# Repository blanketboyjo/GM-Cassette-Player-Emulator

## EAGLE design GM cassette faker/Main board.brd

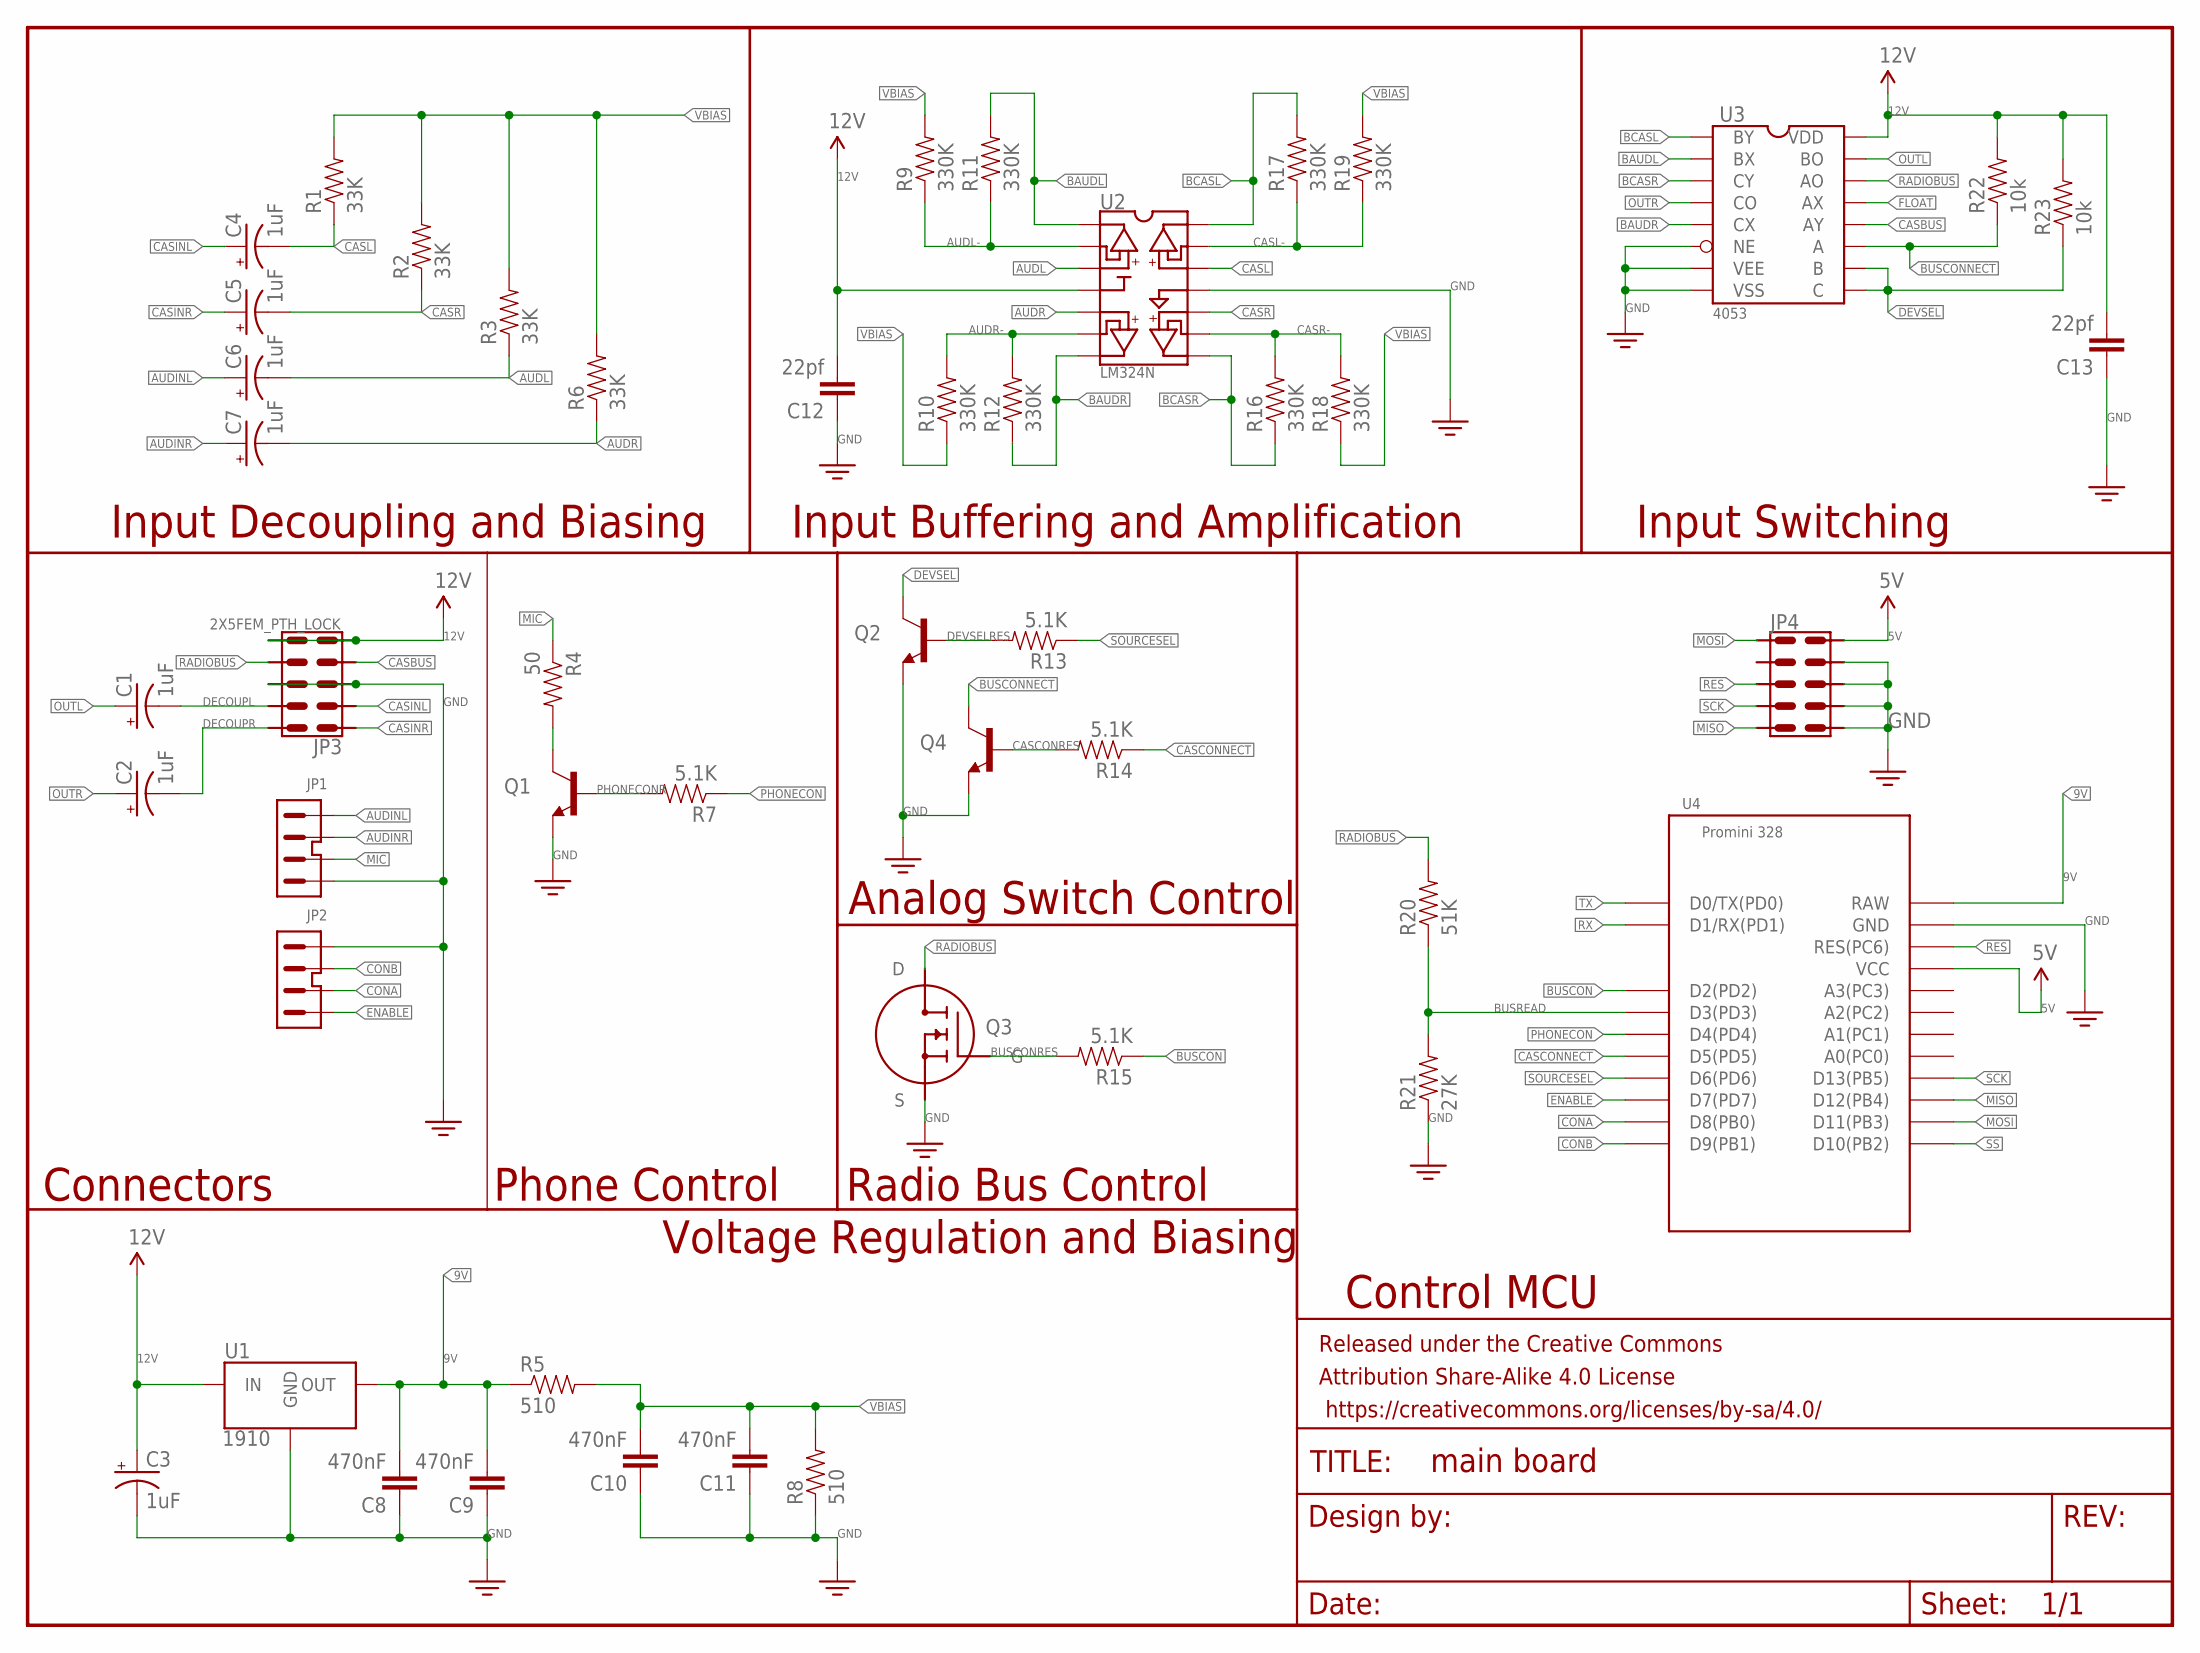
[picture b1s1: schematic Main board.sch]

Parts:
C1, C2, C3, C4, C5, C6, C7: 1uF; CPOL-RADIAL-10UF-25V
C8, C9, C10, C11: 470nF; 0603-CAP
C12, C13: 22pf; 0603-CAP
FRAME1: FRAME-LETTERNO_PACKAGE; DUMMY
JP1, JP2: 4PINJST; JST-4-PTH-VERT
JP3, JP4: 2X5FEM_PTH_LOCK; 2X5PTHFEMLOCK
Q1, Q2, Q4: TRANSISTOR_NPNTO-92-AMMO; TO-92-AMMO
Q3: BUZ101S; TO-220
R1, R2, R3, R6: 33K; 0603-RES
R4: 50; 0603-RES
R5, R8: 510; 0603-RES
R7, R13, R14, R15: 5.1K; 0603-RES
R9, R10, R11, R12, R16, R17, R18, R19: 330K; 0603-RES
R20: 51K; 0603-RES
R21: 27K; 0603-RES
R22, R23: 10k; 0603-RES
U1: 1910; TO-220
U2: LM324N; DIP14
U3: 4053; DIP16
U4: PROMINIV2NOFTDI

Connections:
5V: JP4.P$10, U4.VCC
9V: C8.2, C9.2, R5.1, U1.3 (OUT), U4.RAW
12V: C3.1 (+), C12.2, C13.2, JP3.P$5, JP3.P$6, R22.2, R23.2, U1.1 (IN), U2.P$4 (VCC), U3.P$16 (VDD)
AUDINL: C6.1 (+), JP1.1
AUDINR: C7.1 (+), JP1.2
AUDL: C6.2 (-), R3.1, U2.P$3 (A+)
AUDL-: R9.1, R11.1, U2.P$2 (A-)
AUDR: C7.2 (-), R6.1, U2.P$5 (B+)
AUDR-: R10.2, R12.2, U2.P$6 (B-)
BAUDL: R11.2, U2.P$1 (AO), U3.P$2 (BX)
BAUDR: R12.1, U2.P$7 (BO), U3.P$5 (CX)
BCASL: R17.2, U2.P$14 (DO), U3.P$1 (BY)
BCASR: R16.1, U2.P$8 (CO), U3.P$3 (CY)
BUSCON: R15.1, U4.D2 (D2(PD2))
BUSCONNECT: Q4.3 (C), R22.1, U3.P$11 (A)
BUSCONRES: Q3.1 (G), R15.2
BUSREAD: R20.1, R21.2, U4.D3 (D3(PD3))
CASBUS: JP3.P$4, U3.P$12 (AY)
CASCONNECT: R14.1, U4.D5 (D5(PD5))
CASCONRES: Q4.2 (B), R14.2
CASINL: C4.1 (+), JP3.P$2
CASINR: C5.1 (+), JP3.P$1
CASL: C4.2 (-), R1.1, U2.P$12 (D+)
CASL-: R17.1, R19.1, U2.P$13 (D-)
CASR: C5.2 (-), R2.1, U2.P$10 (C+)
CASR-: R16.2, R18.2, U2.P$9 (C-)
CONA: JP2.3, U4.D8 (D8(PB0))
CONB: JP2.2, U4.D9 (D9(PB1))
DECOUPL: C1.2 (-), JP3.P$9
DECOUPR: C2.2 (-), JP3.P$10
DEVSEL: Q2.3 (C), R23.1, U3.P$9 (C), U3.P$10 (B)
DEVSELRES: Q2.2 (B), R13.2
ENABLE: JP2.4, U4.D7 (D7(PD7))
FLOAT: U3.P$13 (AX)
GND: C3.2 (-), C8.1, C9.1, C10.1, C11.1, C12.1, C13.1, JP1.4, JP2.1, JP3.P$3, JP3.P$8, JP4.P$6, JP4.P$7, JP4.P$8, JP4.P$9, Q1.1 (E), Q2.1 (E), Q3.3 (S), Q4.1 (E), R8.1, R21.1, U1.2 (GND), U2.P$11 (GND), U3.P$6 (NE), U3.P$7 (VEE), U3.P$8 (VSS), U4.GND1 (GND), U4.GND3 (GND)
MIC: JP1.3, R4.1
MISO: JP4.P$5, U4.D12 (D12(PB4))
MOSI: JP4.P$1, U4.D11 (D11(PB3))
unnamed: Q1.3 (C), R4.2
OUTL: C1.1 (+), U3.P$15 (BO)
OUTR: C2.1 (+), U3.P$4 (CO)
PHONECON: R7.1, U4.D4 (D4(PD4))
PHONECONR: Q1.2 (B), R7.2
RADIOBUS: JP3.P$7, Q3.2 (D), R20.2, U3.P$14 (AO)
RES: JP4.P$3, U4.RES1 (RES(PC6)), U4.RES3 (RES(PC6))
RX: U4.D1 (D1/RX(PD1))
SCK: JP4.P$4, U4.D13 (D13(PB5))
SOURCESEL: R13.1, U4.D6 (D6(PD6))
SS: U4.D10 (D10(PB2))
TX: U4.D0 (D0/TX(PD0))
VBIAS: C10.2, C11.2, R1.2, R2.2, R3.2, R5.2, R6.2, R8.2, R9.2, R10.1, R18.1, R19.2

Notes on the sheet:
Voltage Regulation and Biasing
Input Decoupling and Biasing
Input Buffering and Amplification
Input Switching
Control MCU
Analog Switch Control
Radio Bus Control
Connectors
Phone Control

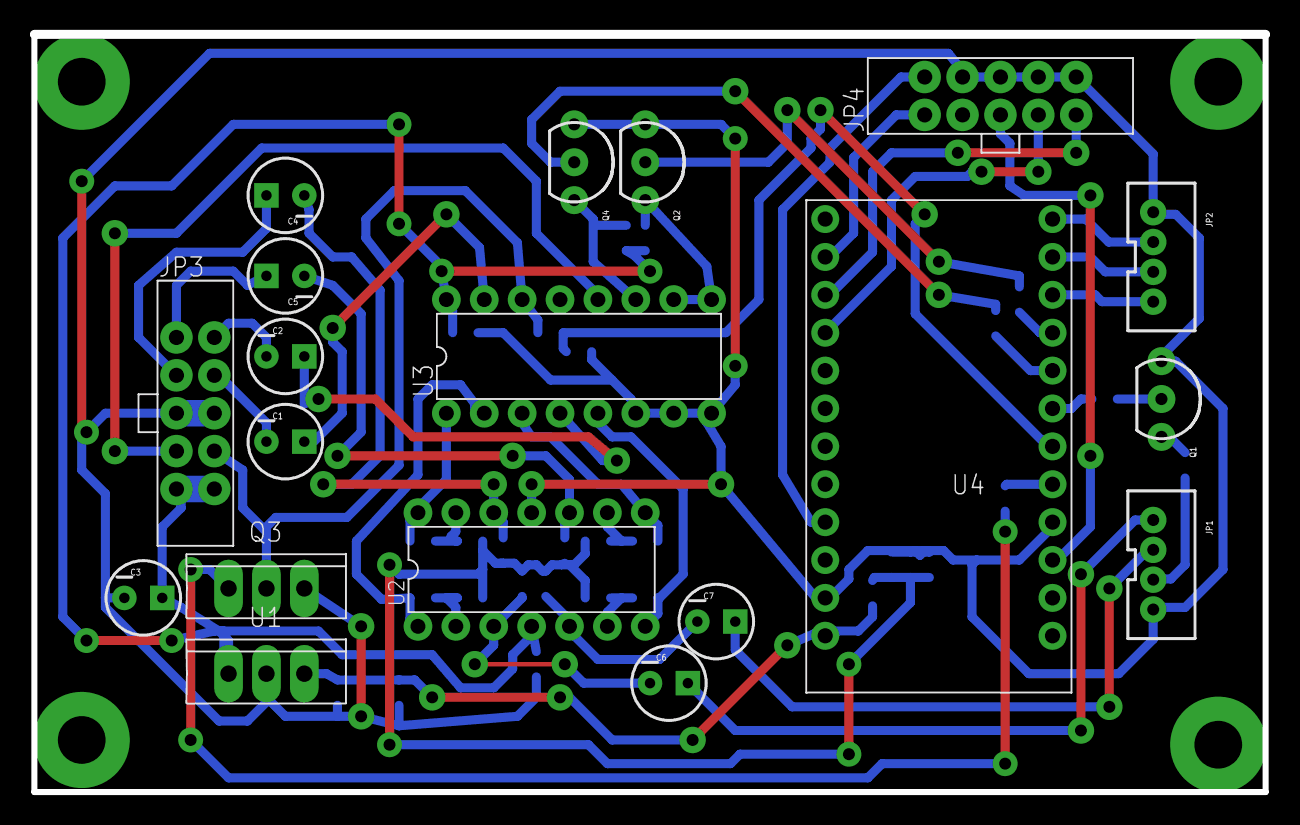
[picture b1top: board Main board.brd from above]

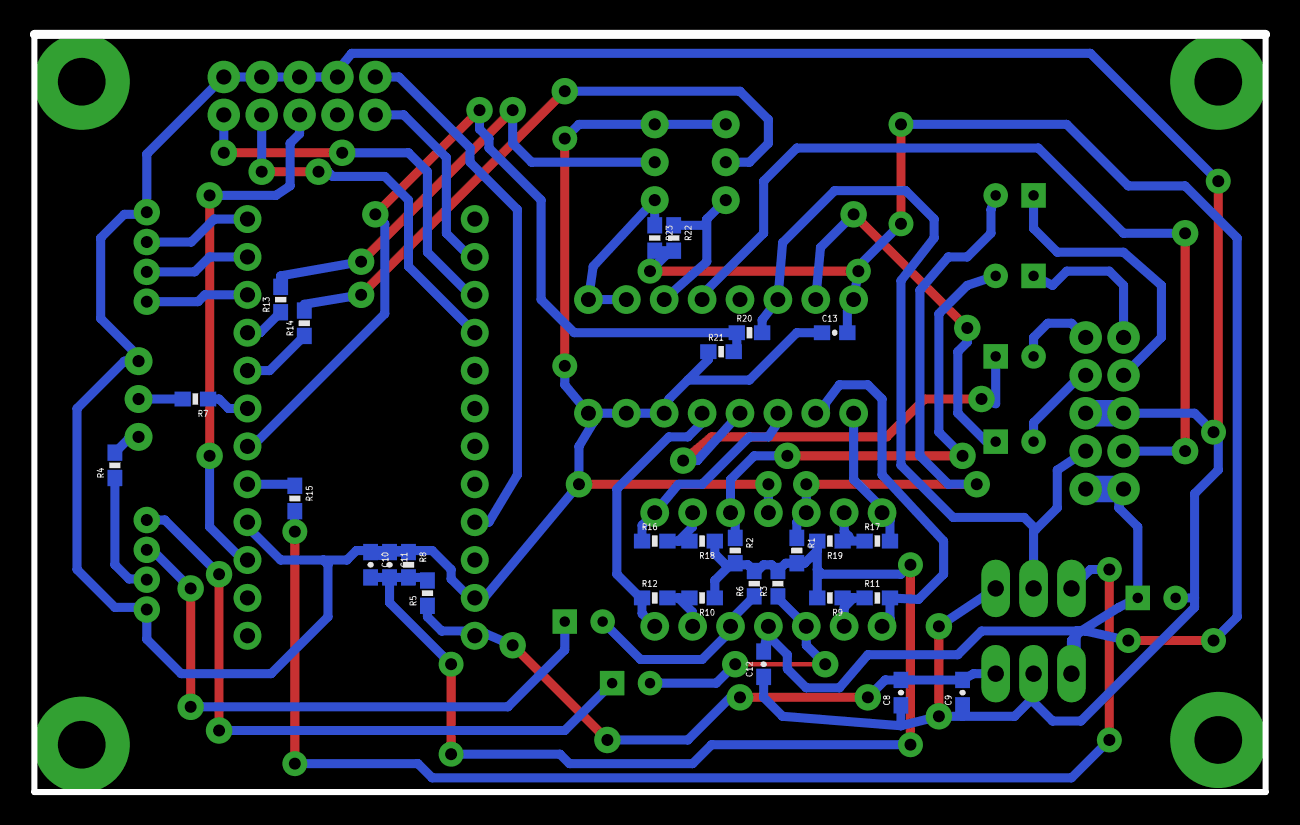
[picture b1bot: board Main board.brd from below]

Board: 2 copper layers, 82.5 x 50.7 mm, 49 parts (29 on the bottom side), 47 nets.

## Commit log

2017-05-09 :lollipop: Added .gitattributes & .gitignore files
2017-05-09 Initial Migration
2017-05-09 Added recorded messages

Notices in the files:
parts and their libraries:
SparkFun-Capacitors: Licensing: Creative Commons ShareAlike 4.0 International - https://creativecommons.org/licenses/by-sa/4.0
SparkFun-Aesthetics: Released under the Creative Commons Attribution Share-Alike 4.0 License
SparkFun-Aesthetics: https://creativecommons.org/licenses/by-sa/4.0
